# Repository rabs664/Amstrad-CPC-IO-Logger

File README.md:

# Amstrad-CPC-IO-Logger

>[!CAUTION]
>USE AT YOUR OWN RISK.
>There is always the risk that this Amstrad CPC IO Logger could cause harm to your CPC. Although I have tested the Amstrad CPC IO Logger, there is no guarantee that it will work properly under all circumstances.

>[!WARNING]
>This project is still in development and has only been made public to share the ideas and solicit feedback. I am no expert in this area and the project should not be used as a baseline example but more an idea of what can be done with the Pico.

## Outline
This Amstrad CPC IO Logger is an external device which allows values written to the Gate Array and the CRTC to be retrieved. This can be useful, for example, for a debugger that exposes the state of these chips in a dedicated UI section.

Port &7F is used by the Gate Array and is write-only. On a standard Amstrad CPC, there is no ability to read back the values sent to the Gate Array (video mode, pen colours, ROM/RAM configuration, etc.). The firmware keeps a shadow copy of all written values in RAM for its own internal use, but many programs bypass the firmware entirely for such operations.

Port &BF can be used to read values from the CRTC, but only on certain CRTC types, and even then, only a subset of registers is readable. The firmware only maintains a shadow copy of R12–R13 (display start address). The remaining registers cannot be read back reliably across all machines, as behaviour varies depending on the CRTC type installed.

## Summary
The Amstrad CPC only uses the top 8 address lines, A8-A15, to address standard IO devices, as illustrated below. For more information please refer to the [CPC Wiki Default IO Port Summary page](https://www.cpcwiki.eu/index.php/Default_I/O_Port_Summary). To see a list of all known ports please refer to the [CPC Wiki IO Port Summary page](https://www.cpcwiki.eu/index.php/I/O_Port_Summary). This Amstrad CPC IO logger then captures A8-A15 and D0-D7 associated with any IO Write that occurs (i.e. a Z80 OUT instruction). Any IO Writes associated with the Gate Array or CRTC are captured and can be retrieved at any point with a series of simple IO Reads to the Amstrad CPC IO logger (i.e. a Z80 IN instruction).

## Design Summary
The discrete 74 series logic associated with Amstrad CPC IO Logger PCB presents two signals* to the Pico;
- IOWR: Active low on an IO Write instruction from the Amstrad CPC
- CSRD: Active low when on an IO read instruction from the Amstrad CPC for the Amstrad CPC IO Logger IO Address.

### Capture
When IOWR goes low, State Machine 1 (SM1) will push the contents of A8-A15** and D0-D7 onto its RX FIFO. DMA1 detects this and places the data into a Capture Buffer. Note that the Capture buffer is configured as a Rig Buffer.

**A0-A1 are also capture but are not used.

The contents of the Capture Buffer is decoded and the CRTC and Gate Array Register write values are placed into a Register Buffer.

### Timing
When data is placed into the Capture Buffer it is timed stamped in the Timing Buffer with time since start in micro seconds.

### Retrieve
When CSRD goes low after an IN instruction (i.e. after INP(&F9E0) from BASIC), SM2 places a transfer count of 1 on it's RX FIFO. DMA2 detects this and places this value into the Transfer Count Trigger of DMA3. DMA3 detects this and then places the next register value from the Register Buffer onto the TX FIFO of SM2. This is then returned back to the Amstrad CPC. Repeated IN instructions will return the next value in the Register Buffer.

### Register Buffer
The Register Buffer is a sequential list of register values written to the CRTC and Gate Array. Each IN instruction to the Amstrad CPC IO Logger will return the next value in the Register Buffer. An OUT instruction of 0 (i.e. OUT &F9E0,0 from BASIC) will reset the sequence back to the first value in the Register Buffer (i.e. CRTC R0). Equally an OUT instruction of 0 to 43 will set the position in the Register Buffer from which the next IN instruction will retrieve data. Note the Register Buffer is 64 bytes in size and a Ring Buffer, so values past 43 (the ERR Register) will return an uninitialized value until the retrieval position wraps.

- LR is the last CRTC Register written to.
- LP is the last GA Pen written to.
- P16 is the Border Pen
- ERR is a decode error flag generated by the Amstrad CPC IO Logger (still under development).

Please refer to the [CPC Wiki CRTC page](https://www.cpcwiki.eu/index.php/CRTC) and [CPC Wiki Gate Array page](https://www.cpcwiki.eu/index.php/Gate_Array) for more information.

### Pen Colour Values
The Pen Colour values returned do not include the 3 bit command value 010. See INKR Values in the Info folder. 

### Debug
Debug output to a console (i.e. putty) can be enabled within the code and controlled from the Amstrad CPC with an OUT instruction between 50 and 57 (i.e. OUT &F9E0,50 will print the contents of the Register Buffer to the console). See the main code for more information.

Debug commands.

| Debug                      |Value| Log Header |
| ---------------------------|-----|------------|
| PRINT_REG_BUFFER           | 50  | REGBF      |
| TOGGLE_PRINT_CRTC_INDEX    | 51  | CRTCI      |
| TOGGLE_PRINT_CRTC_DATA     | 52  | CRTCD      |
| TOGGLE_GA_PEN              | 53  | GAPEN      |
| TOGGLE_GA_COL              | 54  | GACOL      |
| TOGGLE_GA_RMR              | 55  | GARMR      |
| TOGGLE_GA_MMR              | 56  | GAMMR      |
| TOGGLE_GA_RMR2             | 57  | GARM2      |
| TOGGLE_IO_LOG              | 58  | IOLOG      |
| TOGGLE_CRTC_DATA_TIMING_V1 | 59  |            |
| TOGGLE_CRTC_DATA_TIMING_V2 | 60  |            |

### CRTC Register Logging
IO Writes to the CRTC Register Logging can be enabled using OUT &F9E0,60 (OUT &F9E0,60 again will disable the logging).

When enabled the time stamped writes to the CRTC Registered will be loggged over USB. The logging includes a time since last write in micro seconds, the register number, the value written (in hex) and a "lag-o-meter".

The "lag-o-meter" is a value from 1 to 10 indicating the decode lag behind the capture. A value of 1 is no lag and a value of 10 implies the decode has been overrun and data may be lost.

### Debug Command Logging
The logging of debug Commands sent to the CPC IO Logger from the CPC using OUT &F9E0 can be enabled using OUT &F9E0,58.

## Testing
Only first pass testing has so far been completed on an Amstrad CPC 6128 but the concept is working. More comprehensive testing, including error conditions is still to be completed.

Below is the output from the sample BASIC program in the repository.

## IO Address
By default the IO address used in the repository is set to F9E0. The following IO Address can be selected

- F8E0
- F8F0
- F9E0
- F9F0

## Project History
### 06 June 2026
Removed V1.1 of the PCB
### 17 April 2026 
CRTC Register Logging
### 26 June 2026
Found a small problem with the IO Address Selection when sending Debug Commands to the Pico. see  V2.0 in progress
### 24 July 2026
Updated V2.0 of the PCB

## Acknowledgements
- **NoRecess** for the inspiration and support on this project.
- **RHD** members for support and encouragement.
- **Petersfield Men's Shed IT and Electronics Group** members for support and encouragement.
- **CPC Wiki** for the great information.
- **TinWhisker** for the Simple Pico CDC example

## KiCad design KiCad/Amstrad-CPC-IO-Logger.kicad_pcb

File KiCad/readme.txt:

This folder contains the KiCad project

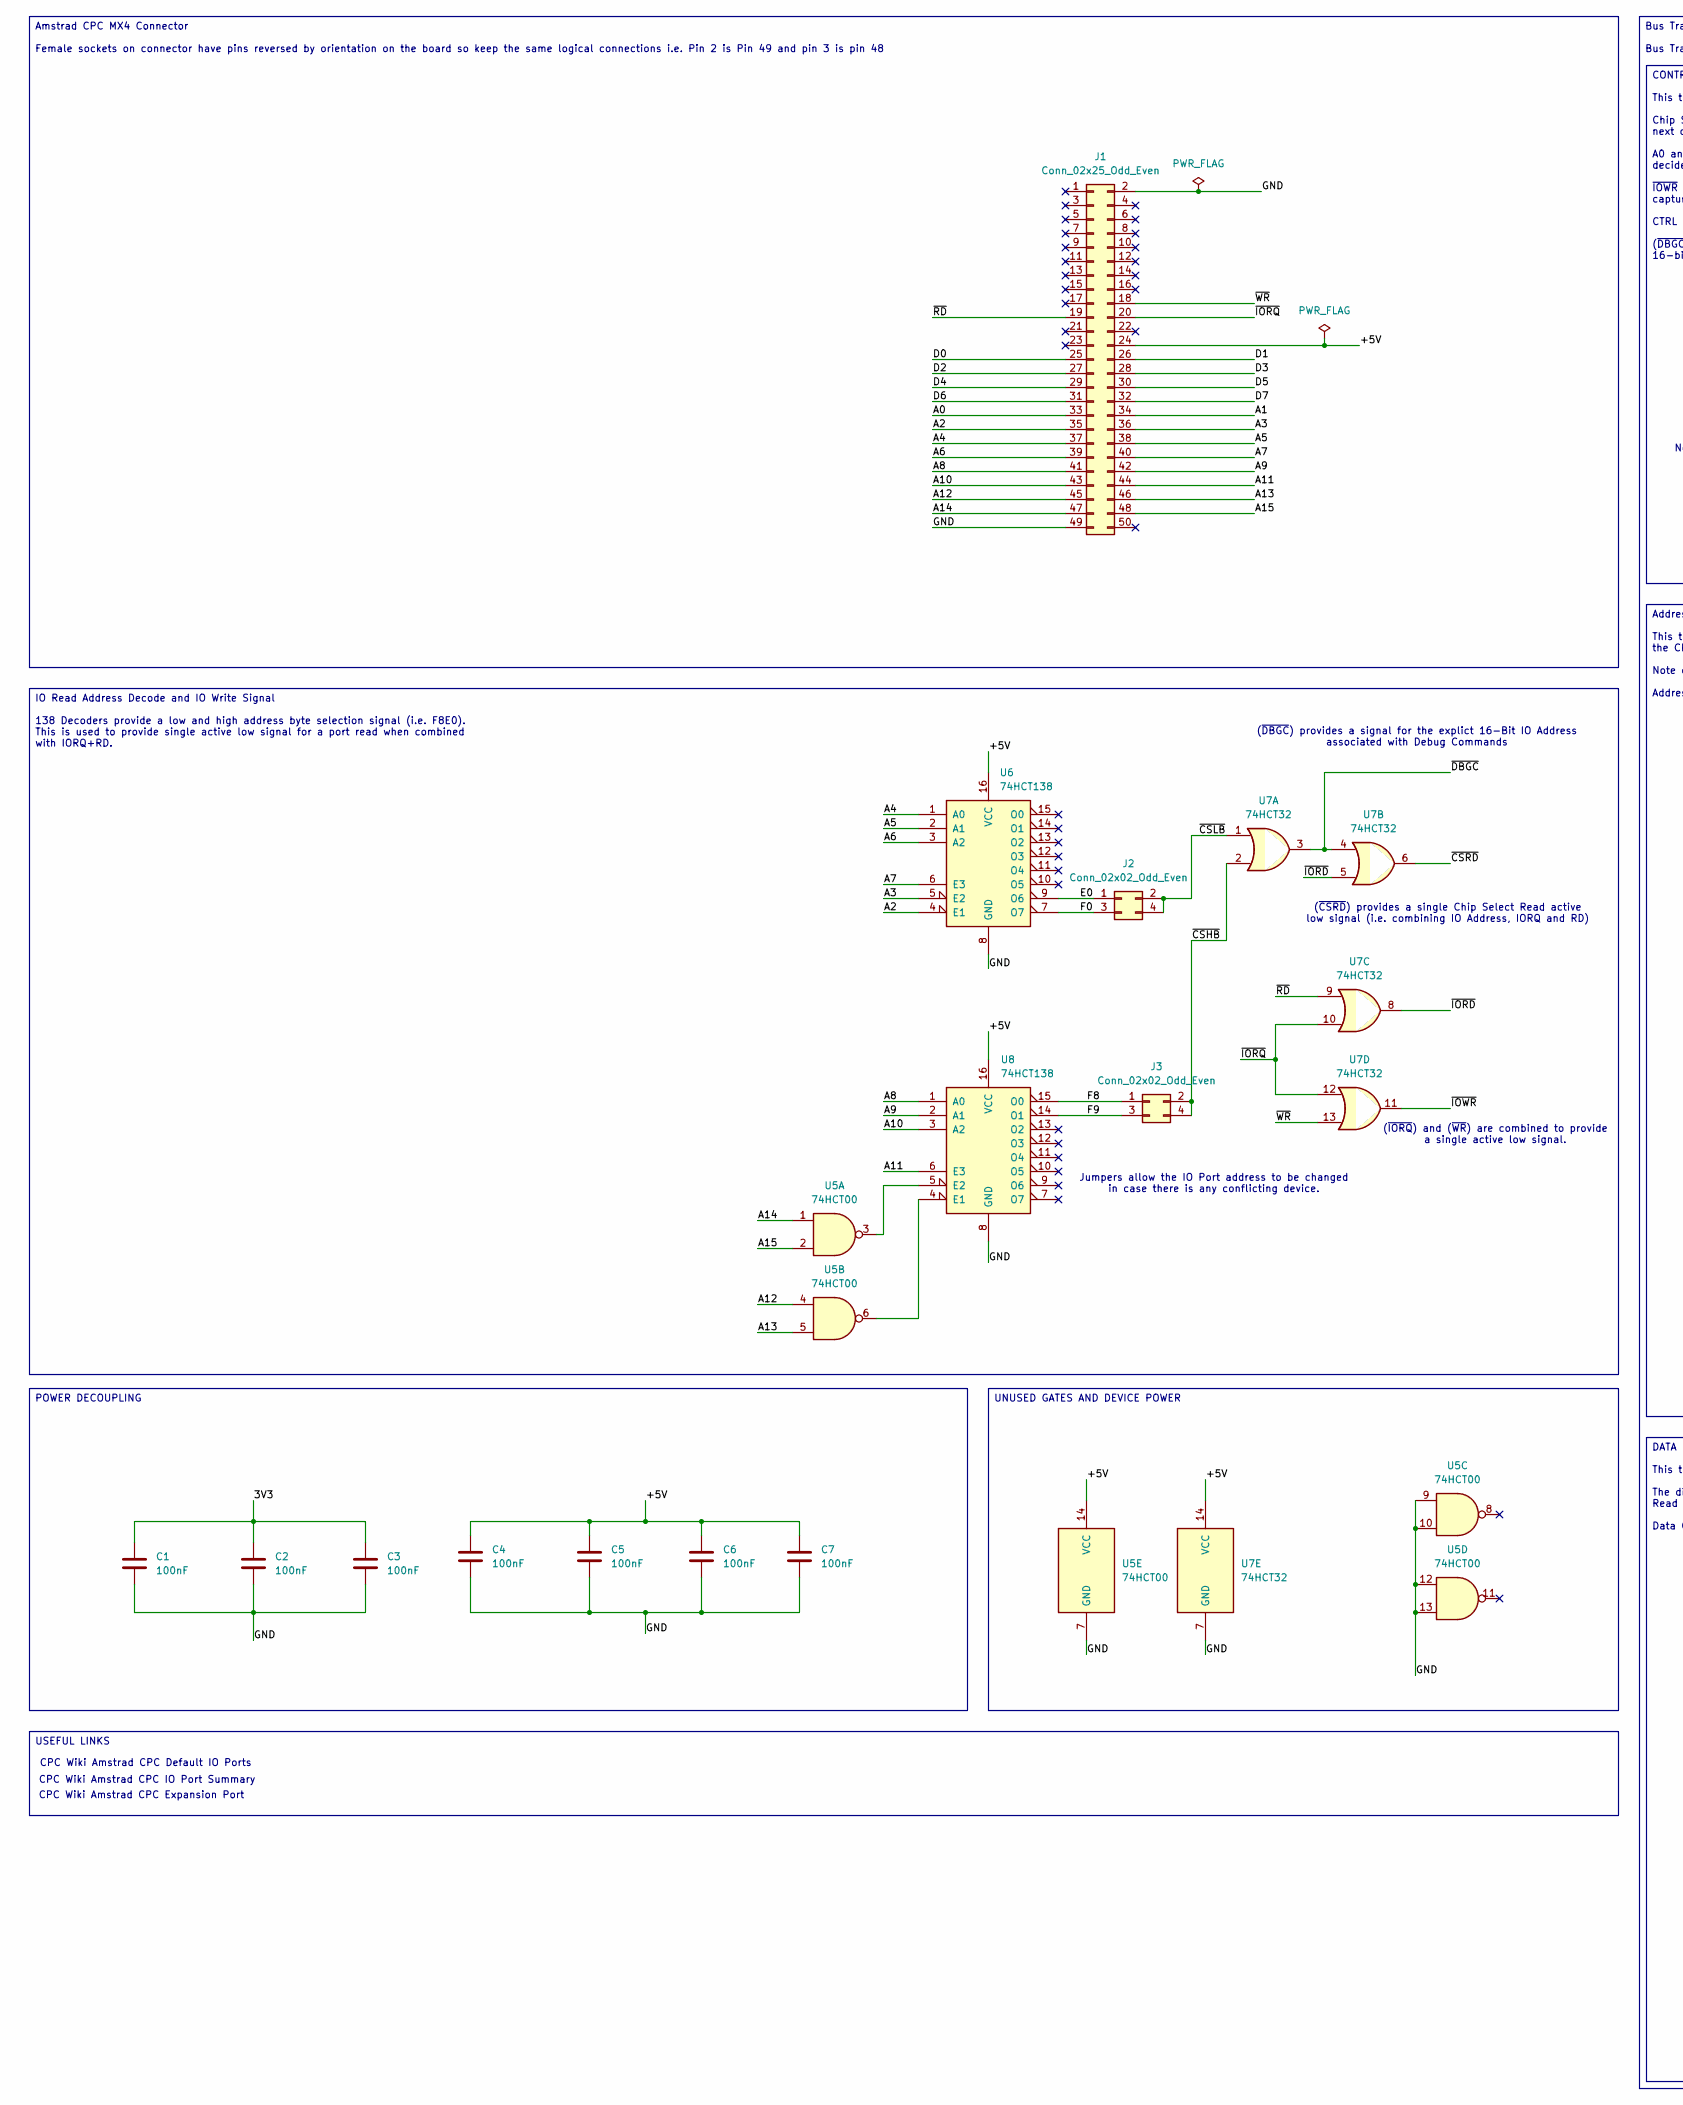
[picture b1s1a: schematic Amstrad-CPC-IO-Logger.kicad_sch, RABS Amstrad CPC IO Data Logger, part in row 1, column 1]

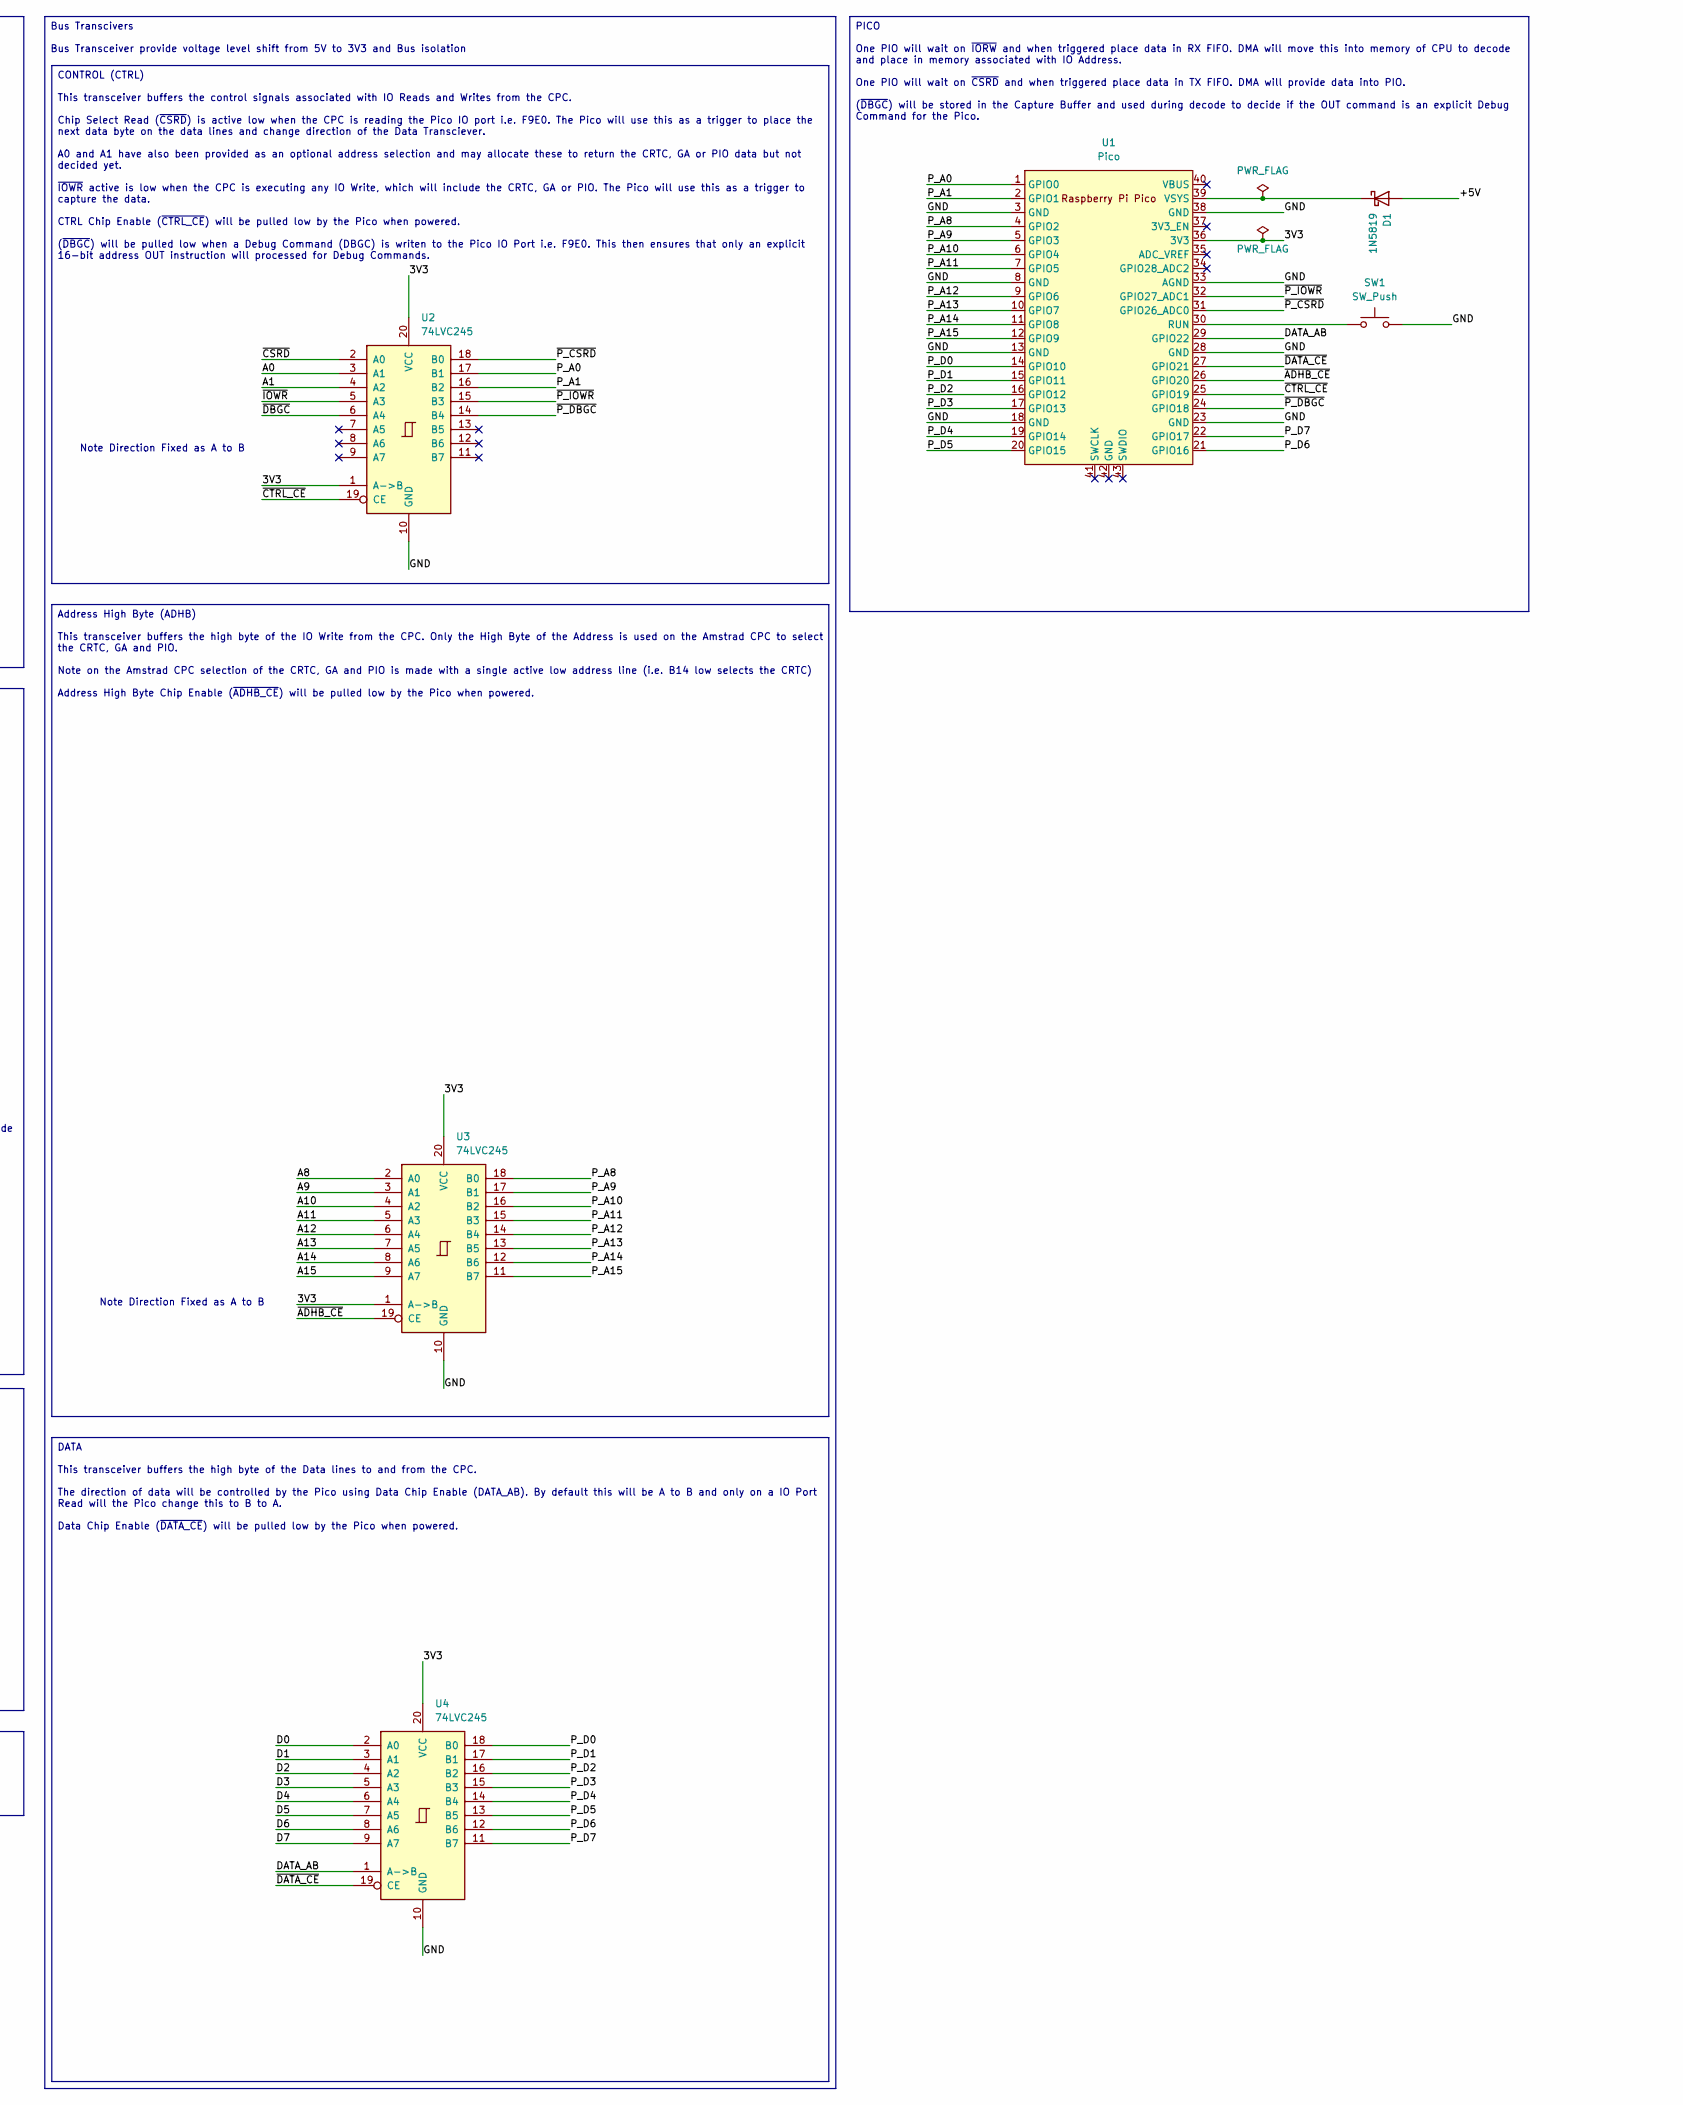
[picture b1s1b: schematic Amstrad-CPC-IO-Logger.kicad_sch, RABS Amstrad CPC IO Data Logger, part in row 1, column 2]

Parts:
C1, C2, C3, C4, C5, C6, C7: 100nF; C_Disc_D5.0mm_W2.5mm_P5.00mm; DigiKey 56-K104K15X7RF53H5G-ND
D1: 1N5819; D_DO-41_SOD81_P10.16mm_Horizontal
J1: Conn_02x25_Odd_Even; IDC-Header_2x25_P2.54mm_Horizontal; DigiKey 3M157291-ND
J2, J3: Conn_02x02_Odd_Even; PinHeader_2x02_P2.54mm_Vertical
SW1: SW_Push; SW_PUSH_6mm
U1: Pico; RPi_Pico_SMD_TH
U2, U3, U4: 74LVC245; DIP-20_W7.62mm_Socket_LongPads
U5: 74HCT00; DIP-14_W7.62mm_Socket_LongPads; DigiKey 296-2081-5-ND
U6, U8: 74HCT138; DIP-16_W7.62mm_Socket_LongPads; DigiKey 296-2091-5-ND
U7: 74HCT32; DIP-14_W7.62mm_Socket_LongPads; Digikey 296-2112-5-ND

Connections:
/3V3: C1.1, C2.1, C3.1, U1.36 (3V3), U2.1 (A->B), U2.20 (VCC), U3.1 (A->B), U3.20 (VCC), U4.20 (VCC)
/+5V: C4.1, C5.1, C6.1, C7.1, D1.2 (A), J1.24, U5.14 (VCC), U6.16 (VCC), U7.14 (VCC), U8.16 (VCC)
/A0: J1.33, U2.3 (A1)
/A1: J1.34, U2.4 (A2)
/A2: J1.35, U6.4 (E1)
/A3: J1.36, U6.5 (E2)
/A4: J1.37, U6.1 (A0)
/A5: J1.38, U6.2 (A1)
/A6: J1.39, U6.3 (A2)
/A7: J1.40, U6.6 (E3)
/A8: J1.41, U3.2 (A0), U8.1 (A0)
/A9: J1.42, U3.3 (A1), U8.2 (A1)
/A10: J1.43, U3.4 (A2), U8.3 (A2)
/A11: J1.44, U3.5 (A3), U8.6 (E3)
/A12: J1.45, U3.6 (A4), U5.4
/A13: J1.46, U3.7 (A5), U5.5
/A14: J1.47, U3.8 (A6), U5.1
/A15: J1.48, U3.9 (A7), U5.2
/D0: J1.25, U4.2 (A0)
/D1: J1.26, U4.3 (A1)
/D2: J1.27, U4.4 (A2)
/D3: J1.28, U4.5 (A3)
/D4: J1.29, U4.6 (A4)
/D5: J1.30, U4.7 (A5)
/D6: J1.31, U4.8 (A6)
/D7: J1.32, U4.9 (A7)
/DATA_AB: U1.29 (GPIO22), U4.1 (A->B)
/E0: J2.1, U6.9 (O6)
/F0: J2.3, U6.7 (O7)
/F8: J3.1, U8.15 (O0)
/F9: J3.3, U8.14 (O1)
/GND: C1.2, C2.2, C3.2, C4.2, C5.2, C6.2, C7.2, J1.2, J1.49, SW1.2, U1.3 (GND), U1.8 (GND), U1.13 (GND), U1.18 (GND), U1.23 (GND), U1.28 (GND), U1.33 (AGND), U1.38 (GND), U2.10 (GND), U3.10 (GND), U4.10 (GND), U5.7 (GND), U5.9, U5.10, U5.12, U5.13, U6.8 (GND), U7.7 (GND), U8.8 (GND)
/P_A0: U1.1 (GPIO0), U2.17 (B1)
/P_A1: U1.2 (GPIO1), U2.16 (B2)
/P_A8: U1.4 (GPIO2), U3.18 (B0)
/P_A9: U1.5 (GPIO3), U3.17 (B1)
/P_A10: U1.6 (GPIO4), U3.16 (B2)
/P_A11: U1.7 (GPIO5), U3.15 (B3)
/P_A12: U1.9 (GPIO6), U3.14 (B4)
/P_A13: U1.10 (GPIO7), U3.13 (B5)
/P_A14: U1.11 (GPIO8), U3.12 (B6)
/P_A15: U1.12 (GPIO9), U3.11 (B7)
/P_D0: U1.14 (GPIO10), U4.18 (B0)
/P_D1: U1.15 (GPIO11), U4.17 (B1)
/P_D2: U1.16 (GPIO12), U4.16 (B2)
/P_D3: U1.17 (GPIO13), U4.15 (B3)
/P_D4: U1.19 (GPIO14), U4.14 (B4)
/P_D5: U1.20 (GPIO15), U4.13 (B5)
/P_D6: U1.21 (GPIO16), U4.12 (B6)
/P_D7: U1.22 (GPIO17), U4.11 (B7)
/~ADHB_CE: U1.26 (GPIO20), U3.19 (CE)
/~CSHB: J3.2, J3.4, U7.2
/~CSLB: J2.2, J2.4, U7.1
/~CSRD: U2.2 (A0), U7.6
/~CTRL_CE: U1.25 (GPIO19), U2.19 (CE)
/~DATA_CE: U1.27 (GPIO21), U4.19 (CE)
/~DBGC: U2.6 (A4), U7.3, U7.4
/~IORD: U7.5, U7.8
/~IORQ: J1.20, U7.10, U7.12
/~IOWR: U2.5 (A3), U7.11
/~P_CSRD: U1.31 (GPIO26_ADC0), U2.18 (B0)
/~P_DBGC: U1.24 (GPIO18), U2.14 (B4)
/~P_IOWR: U1.32 (GPIO27_ADC1), U2.15 (B3)
/~RD: J1.19, U7.9
/~WR: J1.18, U7.13
unnamed: D1.1 (K), U1.39 (VSYS)
unnamed: SW1.1, U1.30 (RUN)
unnamed: U5.6, U8.4 (E1)
unnamed: U5.3, U8.5 (E2)

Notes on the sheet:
CPC Wiki Amstrad CPC Expansion Port
CPC Wiki Amstrad CPC IO Port Summary
Note Direction Fixed as A to B
(~{CSRD}) provides a single Chip Select Read active low signal (i.e. combining IO Address, IORQ and RD)
(~{IORQ}) and (~{WR}) are combined to provide a single active low signal.
CPC Wiki Amstrad CPC Default IO Ports
Jumpers allow the IO Port address to be changed in case there is any conflicting device.
(~{DBGC}) provides a signal for the explict 16-Bit IO Address associated with Debug Commands
Amstrad CPC MX4 Connector Female sockets on connector have pins reversed by orientation on the board so keep the same logical connections i.e. Pin 2 is Pin 49 and pin 3 is pin 48
USEFUL LINKS
UNUSED GATES AND DEVICE POWER
PICO One PIO will wait on ~{IORW} and when triggered place data in RX FIFO. DMA will move this into memory of CPU to decode and place in memory associated with IO Address. One PIO will wait on ~{CSRD} and when triggered place data in TX FIFO. DMA will provide data into PIO. (~{DBGC}) will be stored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
CONTROL (CTRL) This transceiver buffers the control signals associated with IO Reads and Writes from the CPC. Chip Select Read (~{CSRD}) is active low when the CPC is reading the Pico IO port i.e. F9E0. The Pico will use this as a trigger to place the next data byte on the data lines and change dir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
Address High Byte (ADHB) This transceiver buffers the high byte of the IO Write from the CPC. Only the High Byte of the Address is used on the Amstrad CPC to select the CRTC, GA and PIO. Note on the Amstrad CPC selection of the CRTC, GA and PIO is made with a single active low address line (i.e. B1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
DATA This transceiver buffers the high byte of the Data lines to and from the CPC. The direction of data will be controlled by the Pico using Data Chip Enable (DATA_AB). By default this will be A to B and only on a IO Port Read will the Pico change this to B to A. Data Chip Enable (~{DATA_CE}) will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
POWER DECOUPLING
IO Read Address Decode and IO Write Signal 138 Decoders provide a low and high address byte selection signal (i.e. F8E0). This is used to provide single active low signal for a port read when combined with IORQ+RD.
Bus Transcivers Bus Transceiver provide voltage level shift from 5V to 3V3 and Bus isolation

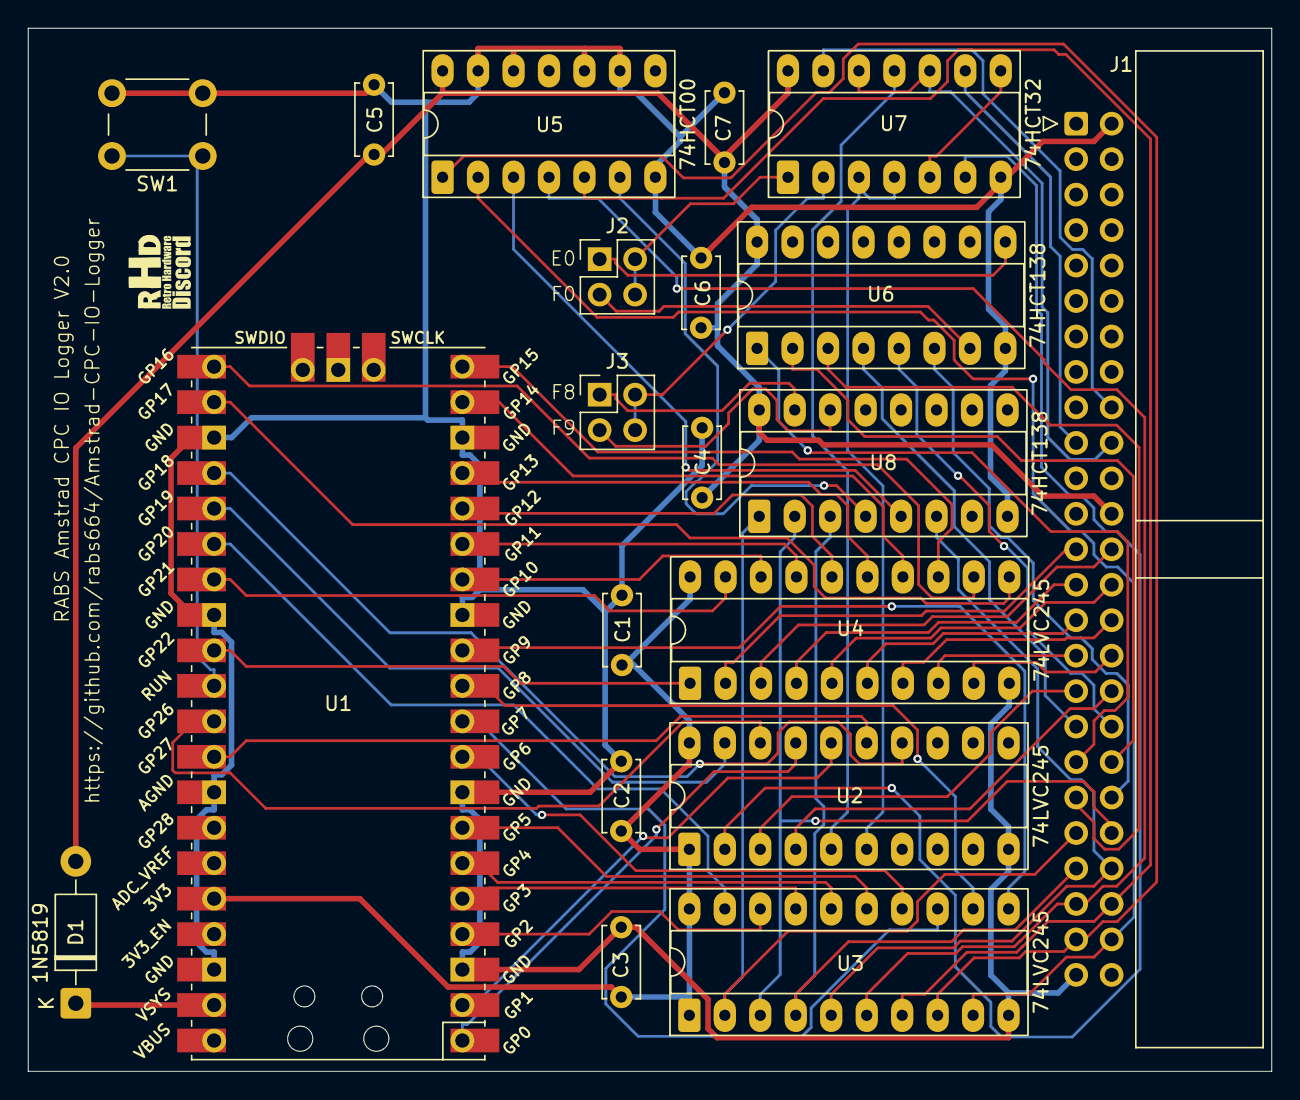
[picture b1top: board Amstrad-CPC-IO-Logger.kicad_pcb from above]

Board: 2 copper layers, 89.1 x 74.7 mm, 20 parts (0 on the bottom side), 69 nets.

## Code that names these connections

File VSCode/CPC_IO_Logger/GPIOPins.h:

/* GPIO Pins for CPC IO Logger */

#include "hardware/pio.h"

#define P_A0 0
#define P_A1 1
#define P_A8 2
#define P_A9 3
#define P_A10 4
#define P_A11 5
#define P_A12 6
#define P_A13 7
#define P_A14 8
#define P_A15 9
#define P_D0 10
#define P_D1 11
#define P_D2 12
#define P_D3 13
#define P_D4 14
#define P_D5 15
#define P_D6 16
#define P_D7 17
#define P_DBGC 18

#define P_IOWR 27
#define P_CSRD 26
#define P_DATA_AB 22
#define P_DATA_CE 21
#define P_ADHB_CE 20
#define P_CTRL_CE 19


void setup_gpio_pins(PIO pio);

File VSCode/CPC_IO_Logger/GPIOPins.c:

/* GPIO Pins for CPC IO Logger */

#include "GPIOPins.h"

void setup_gpio_pins(PIO pio) {
    // PIO IN pins GPIO 0 to GPIO 17 = A0..A1 + A8..A15 + D0..D7 + DBGC
    for (int i = P_A0; i <= P_DBGC; i++) {
        pio_gpio_init(pio,i);
    }

    // GPIO 27 = IOWR, value 0 = active
    pio_gpio_init(pio,P_IOWR);

    // GPIO 22 = DATA_AB, value of 1 = CPC to PICO, 0 = PICO to CPC
    pio_gpio_init(pio,P_DATA_AB);

    // GPIO 26 = CSRD, value 0 = active
    pio_gpio_init(pio,P_CSRD);

}

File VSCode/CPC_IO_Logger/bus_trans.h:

// Bus Transceiver functions and definitions
//
// This file contains the definitions and functions for controlling the bus transceivers
// that are used to interface with the Amstrad CPC. 
//
// The bus transceivers are used to control the direction and enable/disable the data bus, 
// as well as to control the address high byte and control signals. 
//
// The functions in this file will be used to set up the bus transceivers and to control the 
// data bus direction and enable/disable the data bus as needed.    
//
// There are three bus transceivers used in this project:
// 1. Control (CTRL) - This transceiver is used to control the enable/disable of the data bus and to control the direction of the data bus.
// 2. Address High Byte (ADHB) - This transceiver is used to control the address high byte signals.
// 3. Data (DATA) - This transceiver is used to control the data bus signals. 
//
// All three transceivers are controlled using GPIO pins on the Raspberry Pi Pico, 
// and the functions in this file will use the GPIO library to control these pins.
//
// The GPIO pins used for the transceivers are defined as follows:
// CTRL_CE_GPIO - This GPIO pin is used to control the enable/disable of the control transceiver.
// ADHB_CE_GPIO - This GPIO pin is used to control the enable/disable of the address high byte transceiver.
// DATA_CE_GPIO - This GPIO pin is used to control the enable/disable of the data transceiver.
// DATA_DIR_GPIO - This GPIO pin is used to control the direction of the data bus.
//
// The Data Bus direction can be set to either CPC_TO_PICO or PICO_TO_CPC, depending on whether 
// the data is being read from the CPC or written to the CPC.
//
// Below is the layout of the three transceivers and their connections to the GPIO pins:
// 
//         +-----------------------------+
//         |        Control (CTRL)       |
//         |                             |
//         |        CE GPIO: 0           |
//         +-----------------------------+
//         |   Address High Byte (ADHB)  |
//         |                             |
//         |        CE GPIO: 1           |
//         +-----------------------------+
//         |          Data (DATA)        |
//         |                             |
//         |        CE GPIO: 2           |
//         |      Direction GPIO: 3      |
//         +-----------------------------+
//
// Below is layout of the signals conencted to the bus transceivers:
//
//         +-----------------------------+
//         |        Control (CTRL)       |
//         |                             |
//         |        CSRD GPIO: 22        |
//         |        IOWR GPIO: 26        |
//         |        A0   GPIO: 0         |
//         |        A1   GPIO: 1         |
//         +-----------------------------+
//
//         +-----------------------------+
//         |   Address High Byte (ADHB)  |
//         |                             |
//         |        A8   GPIO: 2         |
//         |        A9   GPIO: 3         |
//         |        A10  GPIO: 4         | 
//         |        A11  GPIO: 5         |
//         |        A12  GPIO: 6         |
//         |        A13  GPIO: 7         |
//         |        A14  GPIO: 8         |
//         |        A15  GPIO: 9         |
//         +-----------------------------+
//
//         +-----------------------------+
//         |          Data (DATA)        |
//         |                             |
//         |        D0   GPIO: 10        |
//         |        D1   GPIO: 11        |
//         |        D2   GPIO: 12        |
//         |        D3   GPIO: 13        |
//         |        D4   GPIO: 14        |
//         |        D5   GPIO: 15        |
//         |        D6   GPIO: 16        |
//         |        D7   GPIO: 27        |
//         +-----------------------------+
//


#define ENABLE 0
#define DISABLE 1

// Bus Transceier Direction Control
#define DATA_DIR_GPIO 21

#define CPC_TO_PICO 1
#define PICO_TO_CPC 0

// Bus Transceier setup
// Enable the three bus transceivers
void setup_bus_trans(void);

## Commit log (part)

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2026-04-02 Enhance README with project details and warnings
    Added detailed project information, warnings, and acknowledgements to the README.
2026-04-02 Add readme file for VSCode project
2026-04-02 Add readme for KiCad project
2026-04-02 Initial Create
2026-04-02 Initial build
2026-04-02 Added Files
2026-04-02 Remove original blink.pio
2026-04-02 force build
2026-04-02 Enhance README with images and debug information
    Added images and debug section to README
2026-04-02 Add readme.txt for BASIC software examples
2026-04-02 Fix typo in debug output instruction address
2026-04-02 Update debug output instruction range in README
2026-04-02 Update Register Buffer section in README
    Clarify the description of the Register Buffer and correct minor formatting issues.
2026-04-02 Correct debug output instruction punctuation
    Fixed punctuation in debug output instructions.
2026-04-02 Clarify testing status in README
    Rephrase the testing section for clarity.
2026-04-02 Fix typo in README.md for ERR flag description
2026-04-02 Update image link for Amstrad CPC IO Addressing
2026-04-04 Start of testing
2026-04-04 Start of test changes
2026-04-04 Updated Debug for IO Logger Writes
2026-04-05 Added GGA Pen test
2026-04-05 Added Invalid Pen Test
2026-04-05 RMR Test Added
2026-04-05 Added RMR2 Test and corrected decode logic for it
2026-04-05 corrected error at line 50 for Bank Num
2026-04-06 Added delay after OUT to IO Logger to allow for delay because of debug print statements. Also fixed wrong toggle switch for CRTCI and CRTCD.
2026-04-06 Turn off all Debug statements
2026-04-08 Remove decode of RMR, MMR and RMR2 Registers
2026-04-08 Delete BASIC/list20.bas
    Replaced by list21.bas
2026-04-08 Delete Z80/iolog.dsk
    Not needed
2026-04-08 Delete Z80/rasmoutput.sym
    Not needed
2026-04-08 Change example BASIC program image link
    Updated the image link for the example BASIC program in the README.
2026-04-08 Change Register Buffer V2 image link
    Updated the image link for Register Buffer V2 in README.
2026-04-17 Update to include CRTC Timing
2026-04-17 Enhance README with debug commands and logging info
    Added debug commands and CRTC register logging details to README.
2026-04-28 PCB Update to move the Pico to the edge of the PCB.
2026-06-06 Fix README images and add IO address information
    Updated image links and added IO address section.
2026-06-06 Delete KiCad/Amstrad-CPC-IO-Logger-Gerbers-V1_1.zip
    Removed previous V1.1 of PCB
2026-06-06 Delete KiCad/Amstrad-CPC-IO-Logger-Gerbers-V1_1 directory
    Removed version 1.1 of PCB
2026-06-07 Serial Link Error Reset
2026-06-12 New IOLOG.BAS program and disk file
2026-06-12 Remove wrong disk file.
2026-06-22 Remove TOGGLE_IOLOG entry from README
2026-06-22 Updated comment on IO Log messages
2026-06-22 Enhance README with debug command details
    Added log headers for debug commands and introduced debug command logging section.
2026-06-25 Added excel info sheet on INKR Values
2026-06-25 Removed working excel file
2026-06-25 Rename INKR Values section to Pen Colour Values
    Updated section heading from 'INKR Values' to 'Pen Colour Values' and adjusted the description accordingly.
2026-06-25 Update README with CPC_IO_CAPTURE change note
    Added a note about changing CPC_IO_CAPTURE in IOAddr.h.
2026-06-25 Update README to clarify address usage
    Removed FAE0, FAF0, FBE0, and FBF0 from the list and added notes about F8 and F9 usage.
2026-06-26 Add project history entry for June 26, 2026
    Added project history entry for June 26, 2026, noting an issue with IO Address Selection and linking to Issue 2.
